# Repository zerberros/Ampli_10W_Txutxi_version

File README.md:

Ampli_10W_Txutxi_version
========================

Ampli minimalista de 10W basado en TDA2003 (EoL)

This is the first circuit I've done.
This circuit is based on the test circuit that comes in the datasheet of the TDA2003 but which have removed some components. Nevertheless, has a quality of sound acceptable.
Ideal for carrying music festivals fed by a small battery.
My professor of electronic Txutxi, showed me this circuit,  but must also be in the www.

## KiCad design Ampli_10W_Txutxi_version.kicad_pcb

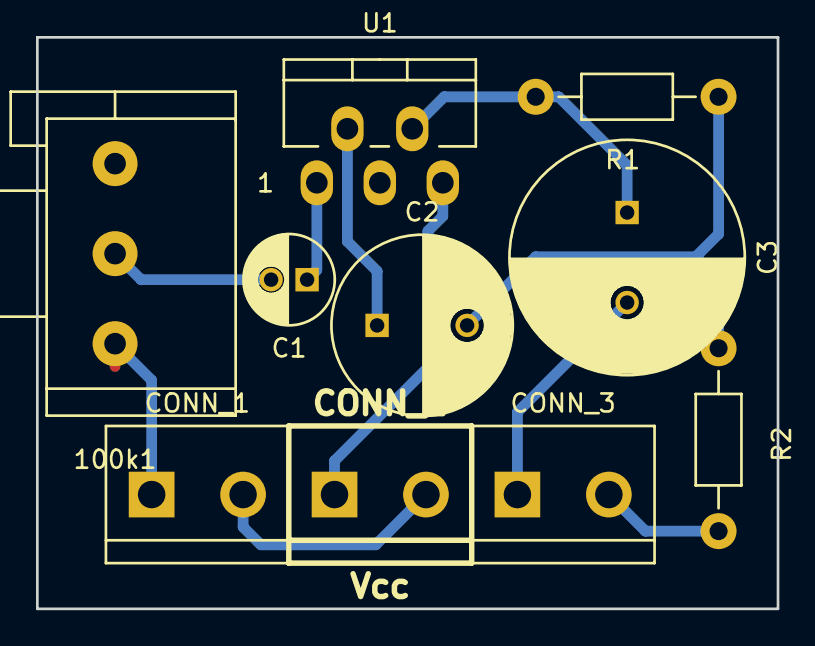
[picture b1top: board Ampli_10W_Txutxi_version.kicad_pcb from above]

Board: 2 copper layers, 41.1 x 31.7 mm, 10 parts (0 on the bottom side), 9 nets.

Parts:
100k1: POT; Potentiometer_Alps-RK16-single
C1: 10uF; C_Radial_D5_L11_P2
C2: 470uF; C_Radial_D10_L16_P5
C3: 1000uF; C_Radial_D13_L21_P5
CONN_1: Audio_In; bornier2
CONN_2: Vcc; bornier2
CONN_3: Carga 4-8 ohm; bornier2
R1: 220; Resistor_Horizontal_RM10mm
R2: 2.2; Resistor_Horizontal_RM10mm
U1: TDA2003V; Pentawatt_Neutral_Staggered_Verical_TO220-5-T05D

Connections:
+9V: CONN_2.1, U1.5
GND: 100k1.3, CONN_1.2, CONN_2.2, CONN_3.2, R2.2, U1.3
unnamed: 100k1.1, CONN_1.1
unnamed: 100k1.2, C1.2
unnamed: C1.1, U1.1
unnamed: C2.1, U1.2
unnamed: C2.2, R1.1, R2.1
unnamed: C3.1, R1.2, U1.4
unnamed: C3.2, CONN_3.1

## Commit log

2014-04-27 Amplifier based on TDA2003
    This is the first circuit I've done.
    This circuit is based on the test circuit that comes in the datasheet of the TDA2003 but which have removed some components. Nevertheless, has a quality of sound acceptable.
    Ideal for carrying music festivals fed by a small battery.
    My electronics teacher Txitxi, showed me this circuit, but must also be in the www.
2014-06-22 Create gh-pages branch via GitHub
2016-03-02 Update library and PCB
